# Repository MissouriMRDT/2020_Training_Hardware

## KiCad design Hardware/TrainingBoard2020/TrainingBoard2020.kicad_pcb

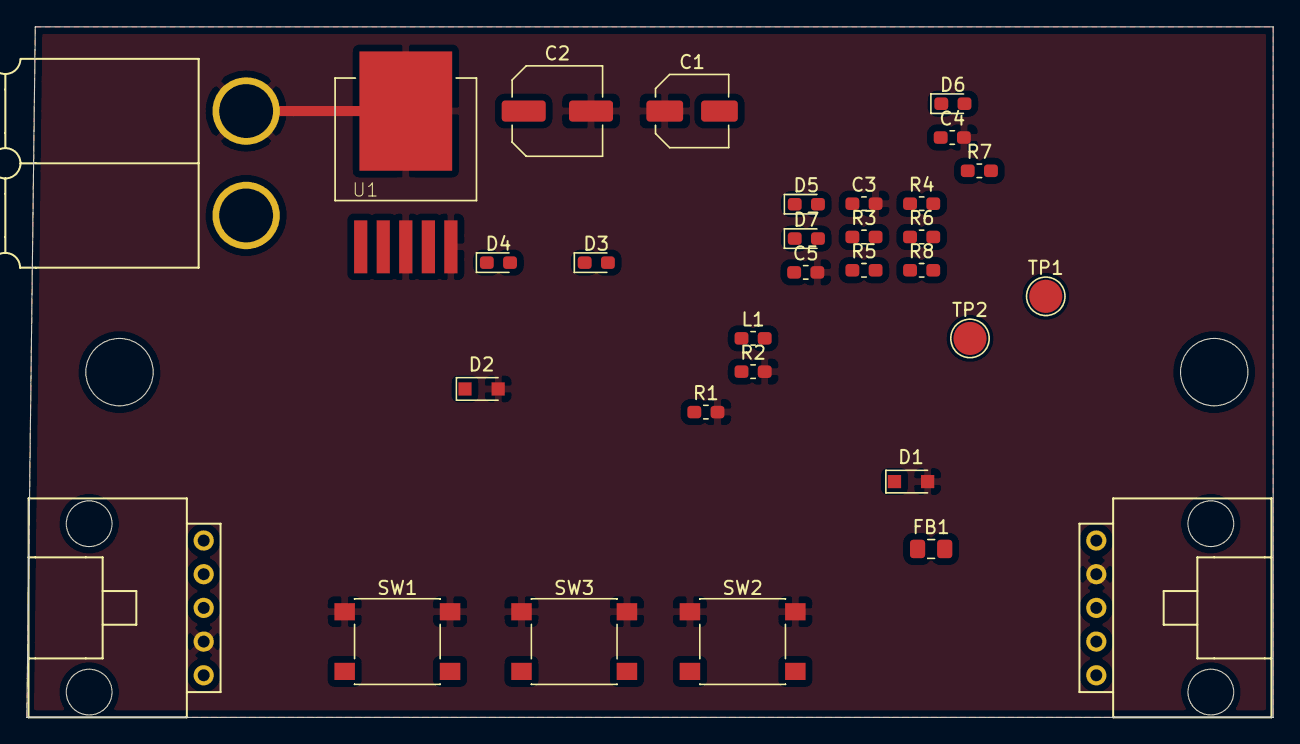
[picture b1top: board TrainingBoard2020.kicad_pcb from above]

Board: 2 copper layers, 94.0 x 52.1 mm, 31 parts (0 on the bottom side), 16 nets.

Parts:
C1: 100uF; C_Elec_5x5.4
C2: 1000uF; C_Elec_6.3x5.4
C3, C4, C5: 0.1uF; C_0603_1608Metric_Pad1.05x0.95mm_HandSolder
Conn1: AndersonPP; Anderson_2_Horizontal_Side_by_Side
Conn2, Conn3: Molex_SL_05; MOLEX_SL_05_Horizontal
D1, D2: D_Zener; D_SOD-323_HandSoldering
D3, D4, D5, D6, D7: LED; LED_0603_1608Metric_Pad1.05x0.95mm_HandSolder
FB1: Ferrite_Bead; C_0805_2012Metric_Pad1.15x1.40mm_HandSolder
L1: 100uH; L_0603_1608Metric_Pad1.05x0.95mm_HandSolder
R1, R3, R4, R5, R6, R7, R8: 1k; R_0603_1608Metric_Pad1.05x0.95mm_HandSolder
R2: 330; R_0603_1608Metric_Pad1.05x0.95mm_HandSolder
SW1, SW2, SW3: SW_Push; SW_Push_1P1T_NO_6x6mm_H9.5mm
TP1, TP2: TestPoint; TestPoint_Pad_D2.5mm
U1: LM2576D2TR4-3.3G; LM2576

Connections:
+3V3: C2.1, Conn2.1, Conn3.1, D4.2, D5.2, D6.2, D7.2, L1.1, TP2.1, U1.4
+12V: C1.2, D3.2, FB1.1, TP1.1, U1.1
/Power/+12v: D1.1, FB1.2
GND: C1.1, C2.2, C3.2, C4.2, C5.2, Conn1.1, Conn2.2, Conn3.2, D1.2, D2.2, R1.2, R2.2, SW1.1, SW2.1, SW3.1, U1.3, U1.5, U1.6
IND_1: C3.1, Conn2.3, Conn3.3, R3.1, R4.2
IND_2: C4.1, Conn2.4, Conn3.4, R5.1, R6.2
IND_3: C5.1, Conn2.5, Conn3.5, R7.1, R8.2
unnamed: D2.1, L1.2, U1.2
unnamed: D3.1, R1.1
unnamed: D4.1, R2.1
unnamed: D5.1, R4.1
unnamed: D6.1, R6.1
unnamed: D7.1, R8.1
unnamed: R3.2, SW1.2
unnamed: R5.2, SW2.2
unnamed: R7.2, SW3.2

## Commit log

2020-09-03 Updating 2020 training board
2020-09-07 Created Training Board
2020-09-07 made board
2020-09-07 blah blah blah
2020-09-07 Added values for buck components
2020-09-07 Finished schematic
2020-09-07 Finished design
2020-09-07 Added annotations
2020-09-07 test
2020-09-19 updated things
2020-09-19 Started design layout of board
    added copper GND layer and started layout and trace routing
2020-09-19 Finished PCB layout
2020-09-20 Didn't save before committing
